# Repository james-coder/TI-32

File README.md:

# TI-32

TI-32 is a hardware + firmware + server enhancement for TI-84+ calculators that adds Wi-Fi-backed features.
An ESP32 board connects to the calculator link port, speaks the TI link protocol, and proxies requests to a local
server for GPT, images, and program downloads.

## Legal and trademark notice

This project is **not** affiliated with, sponsored by, or endorsed by Texas Instruments Incorporated.
“TI”, “TI‑84 Plus”, and related marks are trademarks of Texas Instruments Incorporated; all other
trademarks are the property of their respective owners.

This repository is provided for educational and experimental purposes. Use it at your own risk.
You are responsible for complying with any applicable laws, school or test policies, and device
terms of use. No warranty is provided.

## Project Overview

Core pieces:
- **ESP32 firmware**: `esp32/esp32.ino` handles link protocol, Wi-Fi, and HTTP requests.
- **Calculator launcher**: `programs/LAUNCHER.8xp` is the TI-BASIC UI the user runs.
- **Node server**: `server/` hosts routes for GPT, images, chat, and program downloads.
- **Optional Python server**: `server-py/server.py` is an experimental helper that types into Discord via pyautogui.

## What Is `.mjs`?

`.mjs` files are **Node.js ES modules**. You run them with `node` just like `.js`, but they use the modern `import`
syntax. This repo uses `.mjs` for the server and for build helper scripts.

Examples:
- `node prepareimage.mjs ./test-images/Lenna_(test_image).png`
- `node prepprog.mjs ./programs/LAUNCHER.8xp ./launcher.var`

## Repository Layout (Key Files)

- `esp32/esp32.ino` - ESP32 firmware sketch.
- `esp32/secrets.h` - Wi-Fi + server settings (edit this locally).
- `esp32/launcher.h` - Embedded launcher program (generated).
- `programs/LAUNCHER.8xp` - TI-BASIC launcher program (transfer to calculator).
- `server/index.mjs` - Node/Express server.
- `server/programs/` - Programs served to the calculator.
- `server/images/` - Monochrome image payloads served to the calculator (generated).
- `prepare8xp.mjs` / `prepprog.mjs` - Strip `.8xp` headers and output raw var bytes.
- `prepareimage.mjs` / `image.mjs` - Convert images to TI-84+ monochrome format.
- `preplauncher.sh` - Regenerates `esp32/launcher.h` from the launcher `.8xp`.

## Quick Start

### 1) Configure and build the ESP32 firmware

Prereqs:
- Arduino IDE or Arduino CLI
- ESP32 core installed (esp32:esp32)
- Libraries: **ArTICL** (for `TICL.h`, `CBL2.h`, `TIVar.h`) and **UrlEncode**

Steps:
1. Edit `esp32/secrets.h`:
   - `WIFI_SSID`, `WIFI_PASS`
   - `SERVER` (example: `http://192.168.1.50:8080`)
   - `CHAT_NAME` (short ID shown in chat)
2. Open `esp32/esp32.ino` and select the board (the PCB uses **Seeeduino XIAO ESP32C3**).
   You can purchase the Seeed Studio XIAO ESP32C3 here:
   ```
   https://amzn.to/3NTeTG5
   ```
3. Compile and flash.

#### Flashing a stock Seeeduino XIAO ESP32C3

#### Installing Arduino CLI

macOS/Linux (Homebrew):
```
brew update
brew install arduino-cli
```

macOS/Linux (install script):
```
curl -fsSL https://raw.githubusercontent.com/arduino/arduino-cli/master/install.sh | sh
```
To install into a specific directory:
```
curl -fsSL https://raw.githubusercontent.com/arduino/arduino-cli/master/install.sh | BINDIR=~/local/bin sh
```

Windows:
- Download a prebuilt Arduino CLI binary from the official **Latest release** section and add it to your `PATH`.
- Reference:
  ```
  https://docs.arduino.cc/arduino-cli/installation/#latest-release
  ```
- If you want to use the install script on Windows, run it from Git Bash.

Arduino IDE:
1. Install the ESP32 board package.
2. Select board: `XIAO_ESP32C3`.
3. Select the correct serial port.
4. Click **Upload**.

Arduino CLI:
```
arduino-cli core install esp32:esp32
arduino-cli lib install "UrlEncode"
arduino-cli lib install --git-url https://github.com/KermMartian/ArTICL.git

cp esp32/secrets.h.example esp32/secrets.h
# edit esp32/secrets.h before uploading

arduino-cli compile --fqbn esp32:esp32:XIAO_ESP32C3 esp32
arduino-cli upload -p /dev/ttyACM0 --fqbn esp32:esp32:XIAO_ESP32C3 esp32
```

Optional (smaller firmware, no Bluetooth/mesh):
```
arduino-cli compile --fqbn esp32:esp32:XIAO_ESP32C3 \
  --build-property "compiler.c.elf.libs=@esp32/ld_libs.no_bt_mesh" \
  esp32
```
This only changes the linker library list. On stock ESP32 core libs, BT/mesh archives may still
be pulled in by transitive references.

Use custom core libs built with BT/mesh disabled (slow, extra deps):
```
./scripts/build-esp32-libs.sh
arduino-cli compile --fqbn esp32:esp32:XIAO_ESP32C3 \
  --build-property "runtime.tools.esp32c3-libs.path=.cache/esp32-arduino-libs/esp32c3" \
  --build-property "compiler.c.elf.libs=@esp32/ld_libs.no_bt_mesh" \
  esp32
```
The weak stubs in `esp32/no_bt_mesh_stubs.c` satisfy remaining symbols for local no-BT/mesh builds.

GitHub Actions firmware builds use `PartitionScheme=huge_app` with the default ESP32 core libs.

If upload fails, recheck the port and put the board in bootloader mode, then try again.

#### CI build artifacts

The GitHub Action uploads a build artifact named `esp32-build` that contains the compiled binaries.
You can download it from the Actions run summary.

#### Web flasher (Netlify)

This repo includes a static web flasher in `web-flasher/` built on ESP Web Tools. It uses Web Serial
in Chromium-based browsers to flash a stock Seeeduino XIAO ESP32C3.

Quick setup:
1. Put firmware binaries in `web-flasher/firmware/` as:
   - `bootloader.bin`
   - `partitions.bin`
   - `firmware.bin`
2. Confirm `web-flasher/manifest.json` points to those files.
3. Deploy the folder with Netlify (publish directory: `web-flasher`).

Optional helper to build + copy from Arduino CLI output:
```
./scripts/prepare-web-flasher.sh
```

Notes:
- Requires Chrome/Edge with Web Serial.
- To enter bootloader mode: hold **BOOT**, tap **RESET**, then release **BOOT**.

Release update (optional):
- The workflow `.github/workflows/web-flasher-release.yml` builds firmware on GitHub Release publish.
- It commits the latest firmware binaries + manifest version into `web-flasher/`, so Netlify (Git-connected)
  serves the current release without any Netlify credentials.
- The workflow `.github/workflows/release-artifacts.yml` runs on tag push (`v*`) to create/update a GitHub Release
  and attach the firmware binaries.

#### Wi-Fi setup portal (SoftAP)

On boot, the ESP32 tries to connect using saved credentials (from `secrets.h` or prior setup).
If it can't connect, it starts a SoftAP named `TI-32-SETUP-XXXX` and launches a captive portal.
On most Android/iOS phones the portal opens automatically. If not, browse to `http://192.168.4.1`.
The portal lists nearby access points (tap to fill SSID) and lets you enter credentials.

#### Power management (light sleep)

By default the ESP32 enters light sleep after a short idle period and wakes on TI link activity.
To disable for testing, add this to `esp32/secrets.h`:

```
#define POWER_MGMT_ENABLED 0
```

### 2) Run the server (local machine)

Prereqs:
- Node.js + npm
- `OPENAI_API_KEY` for GPT endpoints
- (Optional) ImageMagick for image conversion scripts

Steps:
1. `cd server`
2. `npm install`
3. Create `server/images` if you plan to use the image features:
   - `mkdir -p server/images`
4. Start the server:
   - `OPENAI_API_KEY=... node index.mjs`
   - Optionally set `PORT` (default is 8080).

The server uses the working directory to locate:
- `server/programs/` for downloadable programs
- `server/images/` for image data
- `server/chat.json` for chat history (auto-created)

### 3) Load the launcher on the calculator

Transfer `programs/LAUNCHER.8xp` to the calculator using your preferred TI transfer tool, then run it.

Tip: The launcher can request an update from the ESP32 (`SETTINGS -> UPDATE`), which sends an embedded program
named `TI32` from the ESP32 to the calculator. That embedded program is generated from `programs/LAUNCHER.8xp`.

## Updating the Launcher

If you change `programs/LAUNCHER.8xp`, regenerate the embedded copy and reflash the ESP32:

```
./preplauncher.sh
```

If you edit `programs/LAUNCHER.8xp.txt`, you must first re-tokenize it into a `.8xp` (see **Editing TI-BASIC
programs** below), then run `./preplauncher.sh`.

## Editing TI-BASIC programs (.8xp <-> .txt)

This repo uses **ti-tools** for reliable conversion between `.8xp` and `.txt`.

Install (requires Rust):
```
git clone https://github.com/cqb13/ti-tools.git
cd ti-tools
cargo build --release
# binary: ./target/release/ti-tools
# or add to PATH:
cargo install --path .
```

Examples:
```
ti-tools convert ./programs/LAUNCHER.8xp -o ./programs/LAUNCHER.8xp.txt
ti-tools convert ./programs/LAUNCHER.8xp.txt -o ./programs/LAUNCHER.8xp
```

You can also use mass mode for directories:
```
ti-tools convert ./programs -o ./programs --mass
```

Helper wrapper:
```
./scripts/ti-tools-convert.sh ./programs/LAUNCHER.8xp ./programs/LAUNCHER.8xp.txt
```

Compare two `.8xp` files while ignoring the 42-byte comment field:
```
./scripts/compare-8xp.py ./programs/LAUNCHER.8xp ./programs/LAUNCHER.roundtrip.8xp
```

### Reproducible `.8xp` Round-Trip Verification

To verify that `.8xp -> .txt -> .8xp` round-tripping works (ignoring the 42-byte comment field that some tools
rewrite), use ti-tools with a consistent display/encode pair and then compare.

Recommended settings:
- `--display-mode accessible`
- `--encode-mode max`

Steps:
1. Convert the original `.8xp` to text:
   ```
   ti-tools convert ./programs/LAUNCHER.8xp -o /tmp/LAUNCHER.8xp.txt --display-mode accessible
   ```
2. Convert the text back to `.8xp`:
   ```
   ti-tools convert /tmp/LAUNCHER.8xp.txt -o /tmp/LAUNCHER.roundtrip.8xp --encode-mode max
   ```
3. Compare while ignoring the comment field:
   ```
   ./scripts/compare-8xp.py ./programs/LAUNCHER.8xp /tmp/LAUNCHER.roundtrip.8xp
   ```

Expected output:
```
MATCH (comment bytes ignored)
```

Note: A byte-for-byte match is not expected because the `.8xp` comment field may be rewritten by the converter.

## Generating Images

To add images for the calculator:

1. Make sure ImageMagick is installed and `server/images` exists.
2. Convert a file:
   ```
   node prepareimage.mjs ./test-images/Lenna_(test_image).png
   ```

This writes a monochrome 96x63 payload into `server/images/`.
Use `./genfiles.sh` to bulk-convert everything in `test-images/`.

## Programs Served by the Server

Drop `.8xp` files into `server/programs/`. The server strips headers on-the-fly using `prepare8xp.mjs` and sends
raw program bytes to the calculator.

## Optional: `server-py`

`server-py/server.py` is a small Flask app that uses `pyautogui` to type into Discord. It is not required for
the core TI-32 flow and should be considered experimental.

## Features to be Added

- Change Wi-Fi settings directly from calculator (PENDING TESTING)
- Watchdog when receiving items (PENDING TESTING)
- Support for color images
- Action text during waiting phase
- Support for multi-page response from GPT
- Support for chat history from GPT
- Support for bigger menu (320x240 resolution only)
- Support for lowercase text
- Basic Web Browsing
- HTTPS Encryption
- Email Send and Read
- Discord Access
- Get local weather
- Control computer wirelessly
- QR Code & Barcode scanner
- Video player

## Bug Fixes

- Images don't work
- GPT Menu closes immediately when receiving response
- App transfer fails

## Video

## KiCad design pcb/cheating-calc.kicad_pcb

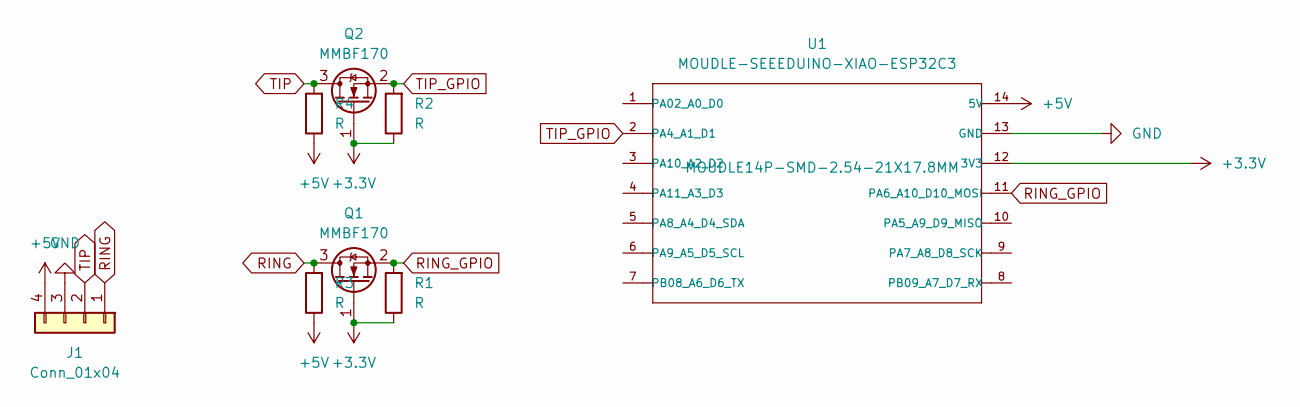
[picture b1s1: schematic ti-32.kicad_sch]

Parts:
J1: Conn_01x04; PinHeader_1x04_P2.54mm_Vertical
Q1, Q2: MMBF170; SOT-23
R1, R2, R3, R4: R; R_Axial_DIN0207_L6.3mm_D2.5mm_P10.16mm_Horizontal
U1: MOUDLE-SEEEDUINO-XIAO-ESP32C3; MOUDLE14P-SMD-2.54-21X17.8MM

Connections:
+3.3V: Q1.1 (G), Q2.1 (G), R1.1, R2.1, U1.12 (3V3)
+5V: J1.4, R3.1, R4.1, U1.14 (5V)
GND: J1.3, U1.13 (GND)
RING: J1.1, Q1.3 (D), R3.2
RING_GPIO: Q1.2 (S), R1.2, U1.11 (PA6_A10_D10_MOSI)
TIP: J1.2, Q2.3 (D), R4.2
TIP_GPIO: Q2.2 (S), R2.2, U1.2 (PA4_A1_D1)

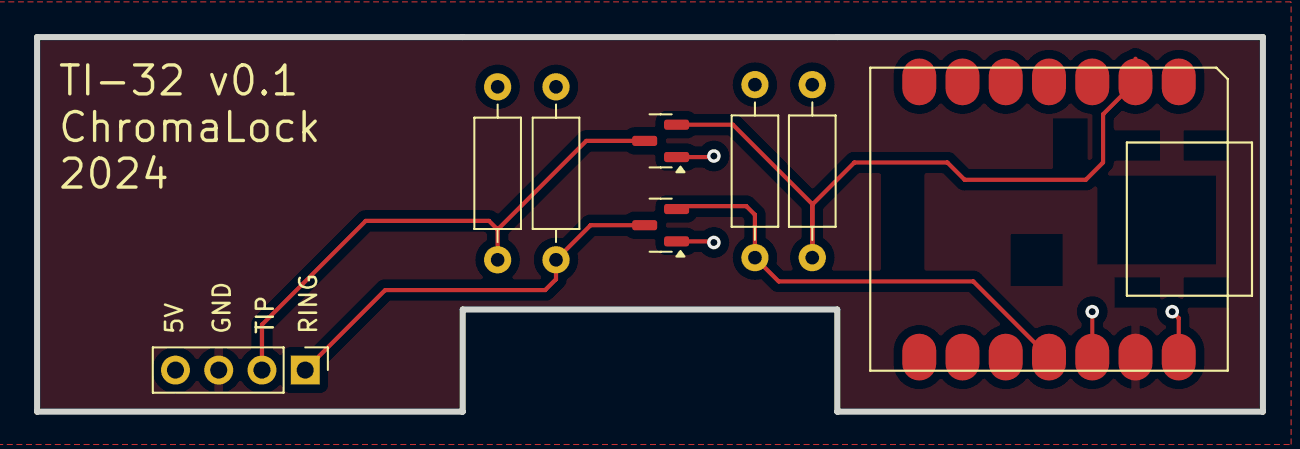
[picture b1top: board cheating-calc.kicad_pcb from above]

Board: 2 copper layers, 72.0 x 22.0 mm, 8 parts (0 on the bottom side), 7 nets.

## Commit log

2026-02-02 Initial import of TI-32 project
    Add firmware, server components, PCB assets, and tooling scripts.
2026-02-02 Add GitHub Action to compile ESP32 sketch
    Set up Arduino CLI with ESP32 core and required libraries.
    Compile esp32 sketch for XIAO ESP32C3 on push/PR/dispatch.
2026-02-02 Expand README with usage and build docs
    Explain .mjs modules, repo layout, and usage flow.
    Document ESP32 build/flash, server setup, launcher updates, and image generation.
2026-02-02 Add receive watchdog for command args
    Track last RX time and time out stuck command arg transfers.
    Fail with a clear rx timeout error instead of hanging.
2026-02-02 Add Wi-Fi setup SoftAP and captive portal
    Persist Wi-Fi/server/chat settings in Preferences.
    Start config portal on boot if STA connect fails, and use saved server settings for requests.
2026-02-02 Add light sleep idle power management
    Enter light sleep after idle link activity, wake on TIP/RING.
    Document how to disable power management for testing.
2026-02-02 Add Python venv requirements for ti-text
    Add requirements.txt and ignore .venv directory.
    Note: ti-text package currently lacks importable module.
2026-02-02 Add ti-tools conversion workflow
    Document ti-tools install and .8xp <-> .txt usage.
    Add a helper script for running ti-tools convert.
2026-02-02 Add .8xp compare helper
    Add a script to compare .8xp files while ignoring the comment field.
    Document the helper in the README.
2026-02-02 Document .8xp round-trip verification
    Add reproducible steps for .8xp -> .txt -> .8xp and compare helper usage.
2026-02-02 Add calculator-driven Wi-Fi setup
    Scan top RSSI networks, encode settings in TI-BASIC, and persist via ESP32.
    Update launcher program and embedded binary for Wi-Fi config flow.
2026-02-03 Rename PCB project files
    Remove legacy ti-32 naming in PCB project artifacts and docs.
2026-02-03 Fix Arduino CLI git library install
    Enable unsafe library installs so --git-url works in CI.
2026-02-03 Add secrets.h template for CI
    Provide an example secrets header and copy it in GitHub Actions when missing.
2026-02-03 Fix GPIO wake level for light sleep
    Use GPIO_INTR_LOW_LEVEL when available for ESP32 Arduino 3.x.
2026-02-03 Fix light sleep indentation
    Align power management block indentation for readability.
2026-02-03 Upload ESP32 build artifacts
    Store Arduino CLI output as a workflow artifact and document flashing steps.
2026-02-03 Document Arduino CLI installation
    Add Homebrew, install script, and Windows notes for Arduino CLI setup.
2026-02-03 Reference Arduino CLI latest release
    Point Windows install instructions at the official latest release section.
2026-02-03 Improve SoftAP portal scan UI
    - add AP scan list with RSSI bars and tap-to-fill SSID
    - enable AP+STA mode and rescan route
    - mark Wi-Fi settings + RX watchdog as pending testing in README
2026-02-03 Tighten GPT output for 16x8 display
    - enforce allowed chars + 128-char cap on ESP32
    - fix GPT display wrapping in TI-BASIC
    - harden HTTP response reads and GPT prompt
2026-02-03 Add Netlify web flasher
    - create web-flasher UI with ESP Web Tools
    - add manifest, firmware placeholder, and Netlify config
    - document web flasher setup and add helper script
2026-02-03 Deploy web flasher on release
    - add Netlify deploy workflow for release tags
    - update web flasher docs with release deploy notes
2026-02-03 Add XIAO ESP32C3 purchase link
    - document board purchase link in README
2026-02-03 Update release workflow for Netlify
    - replace Netlify deploy with repo-updating release workflow
    - adjust web flasher docs for Git-connected Netlify
2026-02-04 Add size report to ESP32 build
    - emit section sizes and map breakdown in CI
2026-02-04 Fix size report map path
    - read map path from correct argv index
2026-02-04 Remove BT/mesh libs from CI builds
    Use a custom linker libs list that omits bt/mesh and add weak stubs to satisfy remaining symbols. CI workflows and web-flasher helper now use the no-bt/mesh list, and README documents the optional bu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
2026-02-04 Add TI trademark and legal notice
    Clarify non-affiliation with Texas Instruments, note trademarks, and add a brief educational-use disclaimer in the README.
2026-02-04 Build custom ESP32 libs without BT/mesh
    Add a lib-builder defconfig and helper script to rebuild esp32c3 libs with BT/mesh disabled, cache them in CI, and compile using the custom libs path. Document the optional flow in README and wire th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
2026-02-04 Fix lib-builder auth in CI
    Unset GITHUB_TOKEN during lib-builder runs to avoid invalid HTTPS auth prompts; allow override via LIB_BUILDER_GITHUB_TOKEN if needed.
2026-02-04 Avoid checkout auth prompts in lib-builder
    Run lib-builder with a clean global git config and disable terminal prompts so public GitHub clones do not request credentials in CI.
2026-02-04 Pass GitHub token to lib-builder
    Provide the Actions token to lib-builder clones using the x-access-token format so public repo fetches do not prompt for credentials in CI.
2026-02-04 Force lib-builder to use espressif repos
    Set AR_USER=espressif for lib-builder runs so arduino-esp32 and esp-idf are cloned from official sources instead of the repo owner.
2026-02-04 Force espressif owner for lib-builder
    Override GITHUB_REPOSITORY_OWNER during lib-builder runs so config.sh uses espressif/arduino-esp32 and esp-idf regardless of the repo owner.
2026-02-04 Build bootloader and mem-variant in lib-builder
    Run copy-bootloader and mem-variant steps after idf-libs so custom libs include required bootloader files; fail fast if bootloader is missing.
2026-02-04 Fallback to core bootloaders in custom libs
    If lib-builder doesn't emit bootloader_*.elf, copy them from the installed Arduino core toolchain so Arduino CLI can still build.
2026-02-05 Backfill memory variants in custom libs
    If lib-builder only emits dio_qspi, copy missing *_qspi/*_opi mem-variant dirs and sdkconfig from the installed Arduino core so sdkconfig.h is available during compile.
2026-02-05 Make BT stubs independent of esp_bt.h
    Avoid including esp_bt.h in no_bt_mesh_stubs.c so builds succeed when BT headers are excluded from custom libs.
2026-02-05 Backfill missing core libs from Arduino toolchain
    If custom lib-builder output is missing libraries like libcoexist.a, copy missing .a files (excluding BT/mesh) plus ld/flags entries from the installed Arduino core libs.
2026-02-05 Use prebuilt ESP32 libs for faster CI
    Add a dedicated esp32-libs-build workflow that publishes a prebuilt libs tarball, and update existing workflows to download it when available before falling back to a local lib-builder run.
2026-02-07 Trigger web-flasher on tag push
    Use tag name for push events
2026-02-07 Update web flasher firmware
    Release: v1.0
2026-02-07 Enforce no BT/mesh linkage in CI
2026-02-07 Make BT/mesh checker work without ripgrep
2026-02-07 Fix size report to ignore discarded map sections
2026-02-07 Use huge_app partition in GitHub firmware builds
2026-02-07 Re-enable default ESP32 libs in CI workflows
